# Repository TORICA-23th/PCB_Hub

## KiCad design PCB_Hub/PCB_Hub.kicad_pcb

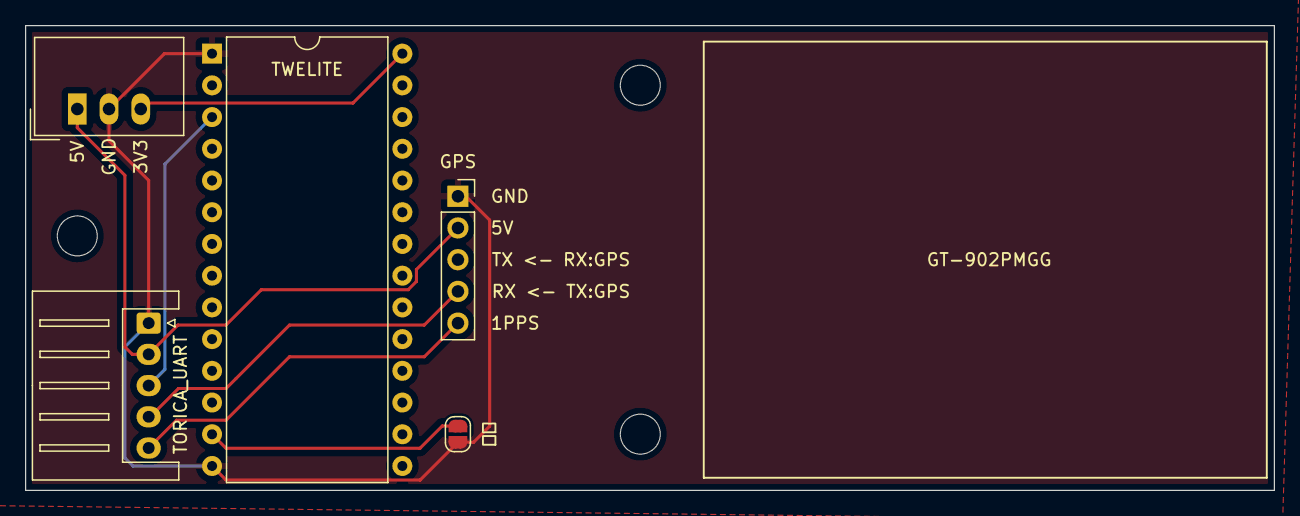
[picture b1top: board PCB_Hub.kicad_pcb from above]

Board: 2 copper layers, 100.0 x 37.2 mm, 5 parts (0 on the bottom side), 7 nets.

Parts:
GPS: GPS; PinSocket_1x05_P2.54mm_Vertical
TORICA_UART: TORICA_UART; JST_XH_S5B-XH-A_1x05_P2.50mm_Horizontal
TWELITE: TWE-L-DP-W; DIP-28_W15.24mm
U1: TSR_1-2433; Converter_DCDC_TRACO_TSR-1_THT
親機: SolderJumper_2_Open; SolderJumper-2_P1.3mm_Open_RoundedPad1.0x1.5mm

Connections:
1PPS: GPS.5, TORICA_UART.5
+3V3: TWELITE.28 (VCC), U1.3 (Vout)
+5V: GPS.2, TORICA_UART.2, U1.1 (Vin)
Due RX: GPS.4, TORICA_UART.4
Due TX: TORICA_UART.3, TWELITE.3 (DIO7/RX)
GND: GPS.1, TORICA_UART.1, TWELITE.1 (GND), TWELITE.14 (GND), U1.2 (GND), 親機.2 (B)
unnamed: TWELITE.13 (DIO10/M1), 親機.1 (A)

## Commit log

2023-04-09 complete Layout
2023-04-13 complete artwork
2023-04-13 complete
